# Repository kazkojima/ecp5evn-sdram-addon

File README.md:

# KiCAD files of a SDR ram addon for ECP5 evaluation board

KiCAD files of a simple RAM addon for Lattice LEF5UM5G-85G

## LiteX/[litex-boards](https://github.com/litex-hub/litex-boards.git) platform hunk of the addon

```
    # SDR SDRAM on connector J39 and J40
    ("sdram_clock", 0, Pins("K5"), IOStandard("LVCMOS33")),
    ("sdram", 0,
        Subsignal("a",     Pins(
            "B10 E7  A11 A19 K4  D14 P1  C14",
            "L1  L2  A9  N2  L3")),
        Subsignal("dq",    Pins(
            "D15 B15 C15 B13 B20 D11 E11 B12",
            "N4  M4  L4  J3  J4  H2  A15 K2")),
        Subsignal("we_n",  Pins("D12")),
        Subsignal("ras_n", Pins("C13")),
        Subsignal("cas_n", Pins("E12")),
        Subsignal("cs_n",  Pins("D13")),
        Subsignal("cke",   Pins("M5")),
        Subsignal("ba",    Pins("E13 A14")),
        Subsignal("dm",    Pins("C12 N3")),
        IOStandard("LVCMOS33"),
        Misc("SLEWRATE=FAST"),
    ),
```

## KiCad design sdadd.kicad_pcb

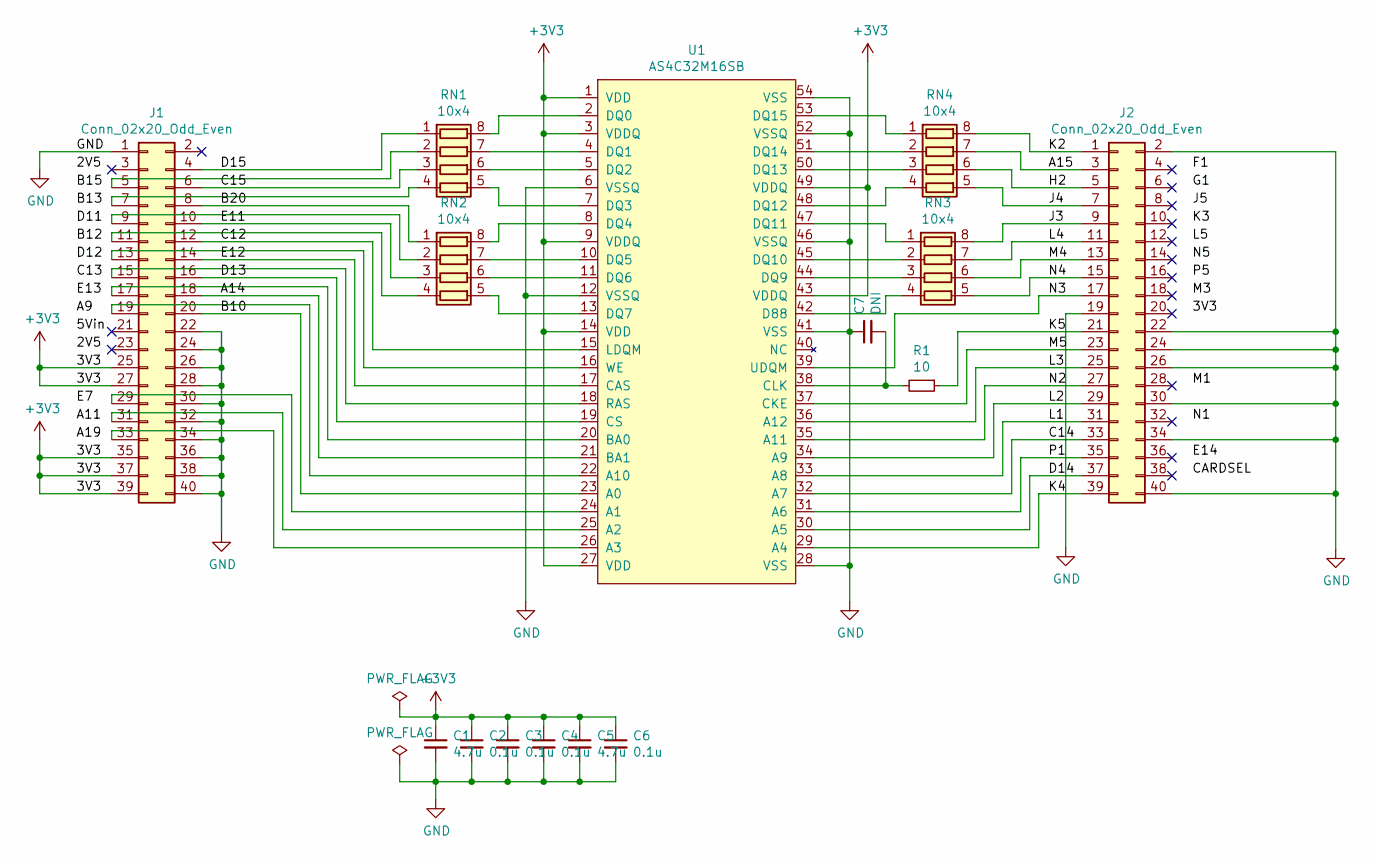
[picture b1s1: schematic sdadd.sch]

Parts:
C1, C5: 4.7u; C_0402_1005Metric
C2, C3, C4, C6: 0.1u; C_0402_1005Metric
C7: DNI; C_0402_1005Metric
J1, J2: Conn_02x20_Odd_Even; PinSocket_2x20_P2.54mm_Vertical
R1: 10; R_0603_1608Metric
RN1, RN2, RN3, RN4: 10x4; R_Array_Concave_4x0603
U1: AS4C32M16SB; TSOP-II-54_22.2x10.16mm_P0.8mm

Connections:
+3V3: C1.1, C2.1, C3.1, C4.1, C5.1, C6.1, J1.25, J1.27, J1.35, J1.37, J1.39, U1.1 (VDD), U1.3 (VDDQ), U1.9 (VDDQ), U1.14 (VDD), U1.27 (VDD), U1.43 (VDDQ), U1.49 (VDDQ)
/A14: J1.18, U1.21 (BA1)
/A15: J2.3, RN4.7 (R2.2)
/B10: J1.20, U1.23 (A0)
/B20: J1.8, RN2.1 (R1.1)
/C12: J1.12, U1.15 (LDQM)
/C14: J2.33, U1.32 (A7)
/C15: J1.6, RN1.3 (R3.1)
/D13: J1.16, U1.19 (CS)
/D14: J2.37, U1.30 (A5)
/D15: J1.4, RN1.1 (R1.1)
/E11: J1.10, RN2.3 (R3.1)
/E12: J1.14, U1.17 (CAS)
/H2: J2.5, RN4.6 (R3.2)
/J3: J2.9, RN3.8 (R1.2)
/J4: J2.7, RN4.5 (R4.2)
/K2: J2.1, RN4.8 (R1.2)
/K4: J2.39, U1.29 (A4)
/K5: J2.21, R1.1
/L1: J2.31, U1.33 (A8)
/L2: J2.29, U1.34 (A9)
/L3: J2.25, U1.36 (A12)
/L4: J2.11, RN3.7 (R2.2)
/M4: J2.13, RN3.6 (R3.2)
/M5: J2.23, U1.37 (CKE)
/N2: J2.27, U1.35 (A11)
/N3: J2.17, U1.39 (UDQM)
/N4: J2.15, RN3.5 (R4.2)
/P1: J2.35, U1.31 (A6)
GND: C1.2, C2.2, C3.2, C4.2, C5.2, C6.2, C7.1, J1.1, J1.22, J1.24, J1.26, J1.28, J1.30, J1.32, J1.34, J1.36, J1.38, J1.40, J2.2, J2.19, J2.22, J2.24, J2.26, J2.30, J2.34, J2.40, U1.6 (VSSQ), U1.12 (VSSQ), U1.28 (VSS), U1.41 (VSS), U1.46 (VSSQ), U1.52 (VSSQ), U1.54 (VSS)
unnamed: C7.2, R1.2, U1.38 (CLK)
unnamed: J1.5, RN1.2 (R2.1)
unnamed: J1.7, RN1.4 (R4.1)
unnamed: J1.9, RN2.2 (R2.1)
unnamed: J1.11, RN2.4 (R4.1)
unnamed: J1.13, U1.16 (WE)
unnamed: J1.15, U1.18 (RAS)
unnamed: J1.17, U1.20 (BA0)
unnamed: J1.19, U1.22 (A10)
unnamed: J1.29, U1.24 (A1)
unnamed: J1.31, U1.25 (A2)
unnamed: J1.33, U1.26 (A3)
unnamed: RN1.5 (R4.2), U1.7 (DQ3)
unnamed: RN1.6 (R3.2), U1.5 (DQ2)
unnamed: RN1.7 (R2.2), U1.4 (DQ1)
unnamed: RN1.8 (R1.2), U1.2 (DQ0)
unnamed: RN2.5 (R4.2), U1.13 (DQ7)
unnamed: RN2.6 (R3.2), U1.11 (DQ6)
unnamed: RN2.7 (R2.2), U1.10 (DQ5)
unnamed: RN2.8 (R1.2), U1.8 (DQ4)
unnamed: RN3.1 (R1.1), U1.47 (DQ11)
unnamed: RN3.2 (R2.1), U1.45 (DQ10)
unnamed: RN3.3 (R3.1), U1.44 (DQ9)
unnamed: RN3.4 (R4.1), U1.42 (D88)
unnamed: RN4.1 (R1.1), U1.53 (DQ15)
unnamed: RN4.2 (R2.1), U1.51 (DQ14)
unnamed: RN4.3 (R3.1), U1.50 (DQ13)
unnamed: RN4.4 (R4.1), U1.48 (DQ12)

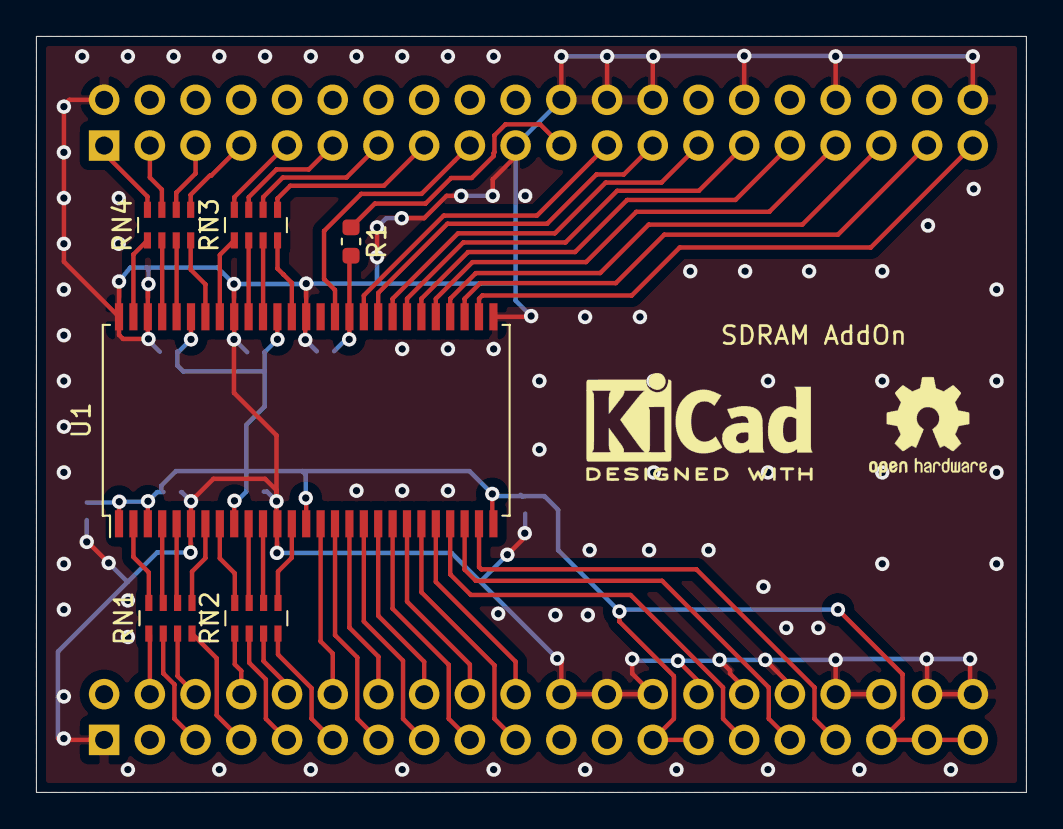
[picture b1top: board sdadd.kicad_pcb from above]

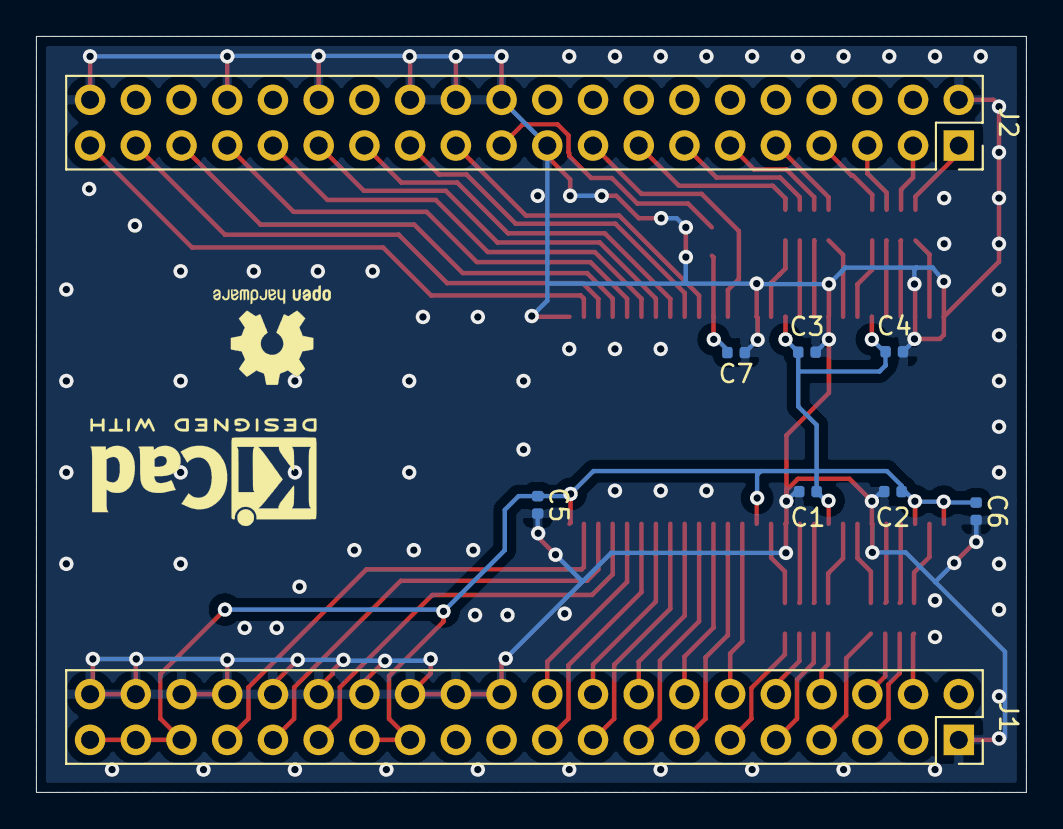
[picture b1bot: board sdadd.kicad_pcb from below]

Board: 2 copper layers, 55.0 x 42.0 mm, 15 parts (9 on the bottom side), 58 nets.

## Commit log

2021-04-16 Initial commit.
2021-04-16 Fix URL.
